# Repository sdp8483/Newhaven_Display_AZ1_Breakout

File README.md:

# Breakout PCB for Newhaven Display AZ1 Series

official breakout board: https://newhavendisplay.com/thru-hole-breakout-board-for-128x32-a1z-cog-with-rgb-support/

## Directory Outline
- [`~/firmware/`](firmware): firmware source code and binaries.
- [`~/mechanical/`](mechanical): mechanical CAD design files, for example the enclosure.
    - [`~/mechanical/3d_files/`](mechanical/3d_files): files exported from CAD for import into 3D printer slicing software.
- [`~/pcb/`](pcb): KiCAD design files. When starting a new KiCAD project in this directory be sure to uncheck *Create a new directory for the project* in the **Create New Project** window.
    - [`/pcb/3d_models`](pcb/3d_models)

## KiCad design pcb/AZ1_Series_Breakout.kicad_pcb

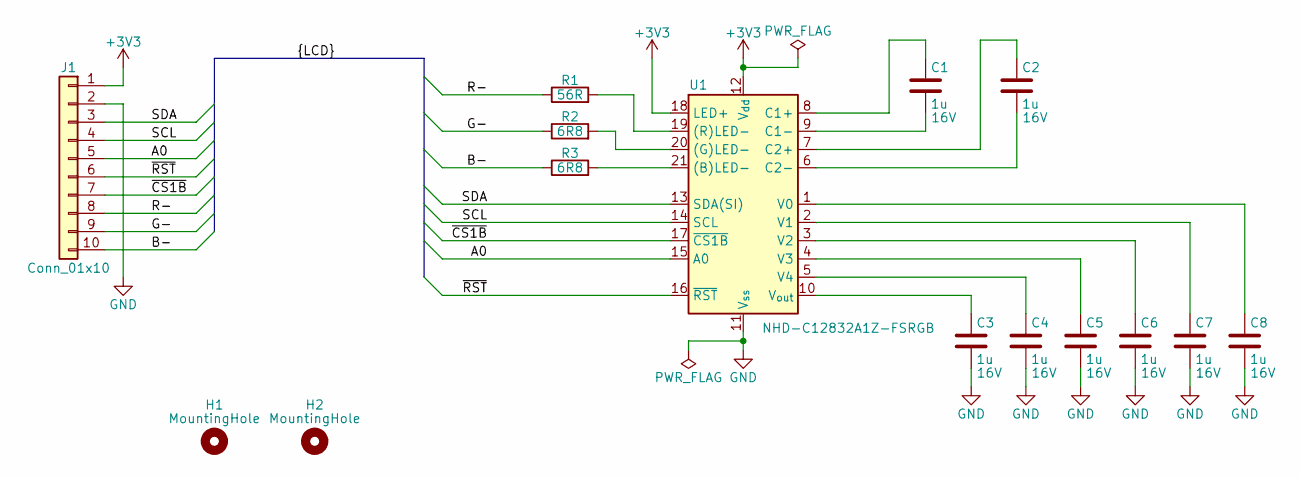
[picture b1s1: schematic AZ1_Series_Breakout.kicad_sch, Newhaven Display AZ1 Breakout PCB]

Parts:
C1, C2, C3, C4, C5, C6, C7, C8: 1u; C_0805_2012Metric; Voltage 16V
H1, H2: MountingHole; MountingHole_3.2mm_M3_DIN965_Pad
J1: Conn_01x10; PinHeader_1x10_P2.54mm_Vertical
R1: 56R; R_0805_2012Metric
R2, R3: 6R8; R_0805_2012Metric
U1: NHD-C12832A1Z-FSRGB

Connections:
+3V3: J1.1, U1.12 (V_{dd}), U1.18 (LED+)
/A0: J1.5, U1.15 (A0)
/B-: J1.10, R3.1
/G-: J1.9, R2.1
/R-: J1.8, R1.1
/SCL: J1.4, U1.14 (SCL)
/SDA: J1.3, U1.13 (SDA(SI))
/~CS1B: J1.7, U1.17 (~CS1B)
/~RST: J1.6, U1.16 (~RST)
GND: C3.2, C4.2, C5.2, C6.2, C7.2, C8.2, J1.2, U1.11 (V_{ss})
unnamed: R3.2, U1.21 ((B)LED-)
unnamed: R2.2, U1.20 ((G)LED-)
unnamed: R1.2, U1.19 ((R)LED-)
unnamed: C1.1, U1.8 (C1+)
unnamed: C1.2, U1.9 (C1-)
unnamed: C2.1, U1.7 (C2+)
unnamed: C2.2, U1.6 (C2-)
unnamed: C8.1, U1.1 (V0)
unnamed: C7.1, U1.2 (V1)
unnamed: C6.1, U1.3 (V2)
unnamed: C5.1, U1.4 (V3)
unnamed: C4.1, U1.5 (V4)
unnamed: C3.1, U1.10 (V_{out})

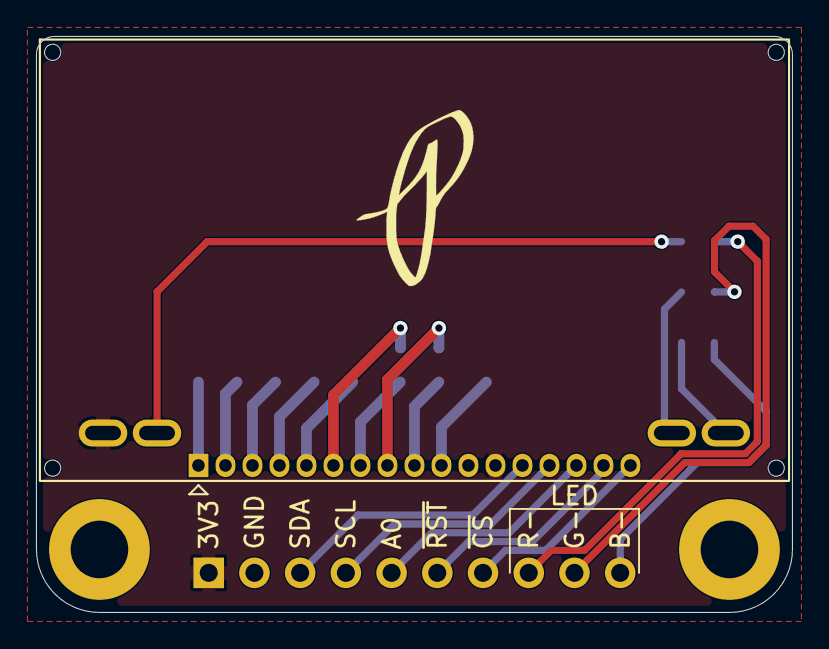
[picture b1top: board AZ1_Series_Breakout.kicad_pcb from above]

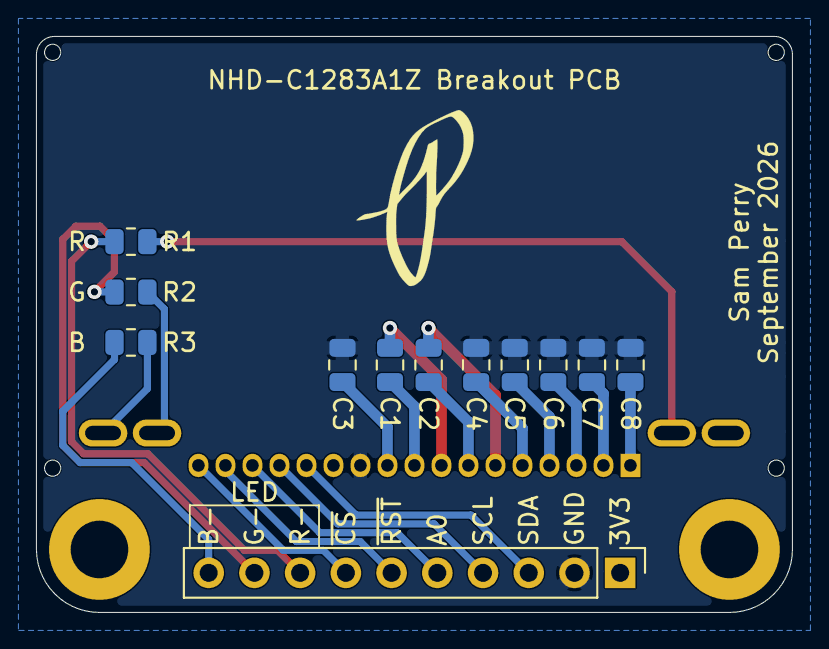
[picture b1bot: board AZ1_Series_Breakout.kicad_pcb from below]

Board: 2 copper layers, 42.0 x 32.0 mm, 15 parts (12 on the bottom side), 23 nets.
